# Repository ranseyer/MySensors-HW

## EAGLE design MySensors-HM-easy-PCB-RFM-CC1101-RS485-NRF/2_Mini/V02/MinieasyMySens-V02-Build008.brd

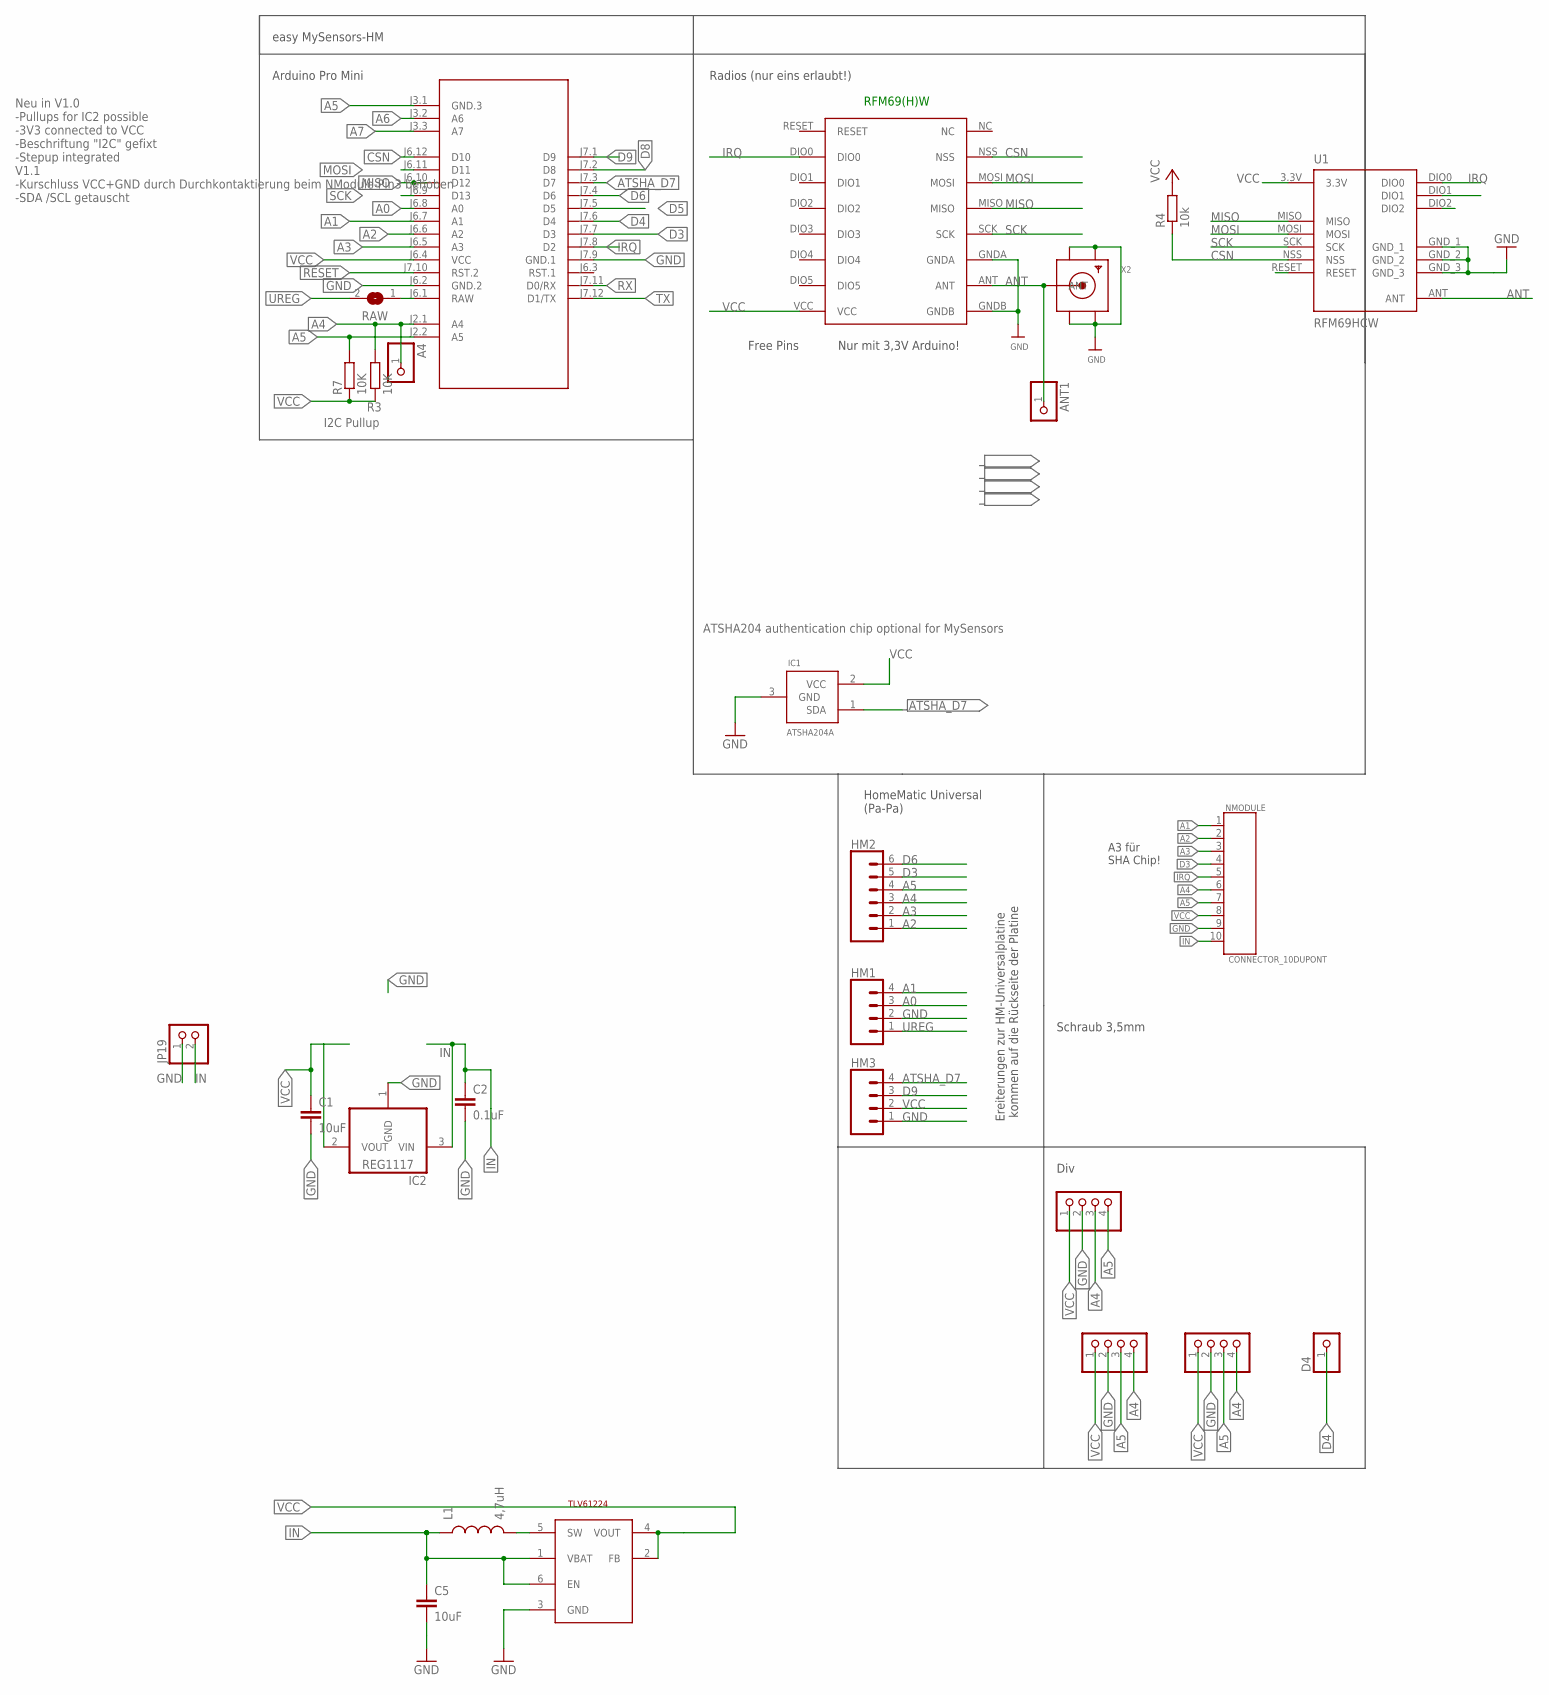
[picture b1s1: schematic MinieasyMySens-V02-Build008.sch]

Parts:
A4: PINHD-1X1; 1X01
ANT1: PINHD-1X1; 1X01
BH1750: PINHD-1X04_2.54-S; 1X04-S
C1: 10uF; C1210
C2: 0.1uF; C1206
C5: 10uF; 0805
D4: PINHD-1X1; 1X01
HM1, HM3: CONN_04; 1X04
HM2: CONN_06SILK_FEMALE_PTH; 1X06
I2C-1, I2C-2: PINHD-1X04_2.54-S; 1X04-S
IC1: ATSHA204A; SOT23
IC2: REG1117; SOT223
JP19: PINHD-1X2; 1X02
L1: 4,7uH; 0805
M1: ARDUINO-PRO-MINI-3.3V#NP; ARDUINO-PRO-MINI#NP
NMODULE: CONNECTOR_10DUPONT; DUPONT_10
R3, R7: 10K; R0805
R4: 10k; M0805
RAW: SJ
RFM69W: RFM69HW; RFM
STEPUP: TLV61224; SOT23-6L
U1: RFM69HCW; RFM69HCW-XXXS2
X2: SMACONNECTOR_EDGE; SMA_EDGELAUNCH

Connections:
A0: HM1.3, M1.J6.8 (A0)
A1: HM1.4, M1.J6.7 (A1), NMODULE.1
A2: HM2.1, M1.J6.6 (A2), NMODULE.2
A3: HM2.2, M1.J6.5 (A3), NMODULE.3
A4: A4.1, BH1750.4, HM2.3, I2C-1.4, I2C-2.3, M1.J2.1 (A4), NMODULE.6, R3.2
A5: BH1750.3, HM2.4, I2C-1.3, I2C-2.4, M1.J2.2 (A5), M1.J3.1 (GND.3), NMODULE.7, R7.2
A6: M1.J3.2 (A6)
A7: M1.J3.3 (A7)
ANT: ANT1.1, RFM69W.ANT, U1.ANT, X2.P (ANT)
ATSHA_D7: HM3.4, IC1.1 (SDA), M1.J7.3 (D7)
CSN: M1.J6.12 (D10), R4.1, RFM69W.NSS, U1.NSS
D3: HM2.5, M1.J7.7 (D3), NMODULE.4
D4: D4.1, M1.J7.6 (D4)
D5: M1.J7.5 (D5)
D6: HM2.6, M1.J7.4 (D6)
D8: M1.J7.2 (D8)
D9: HM3.3, M1.J7.1 (D9)
GND: BH1750.2, C1.2, C2.2, C5.2, HM1.2, HM3.1, I2C-1.2, I2C-2.2, IC1.3 (GND), IC2.1 (GND), JP19.1, M1.J6.2 (GND.2), M1.J7.9 (GND.1), NMODULE.9, RFM69W.GNDA, RFM69W.GNDB, STEPUP.3 (GND), U1.GND_1, U1.GND_2, U1.GND_3, X2.GND@1 (GND4), X2.GND@2 (GND3), X2.GND@3 (GND2), X2.GND@4 (GND1)
IN: C2.1, C5.1, IC2.3 (VIN), JP19.2, L1.1, NMODULE.10, STEPUP.1 (VBAT), STEPUP.6 (EN)
IRQ: M1.J7.8 (D2), NMODULE.5, RFM69W.DIO0, U1.DIO0
MISO: M1.J6.10 (D12), RFM69W.MISO, U1.MISO
MOSI: M1.J6.11 (D11), RFM69W.MOSI, U1.MOSI
unnamed: L1.2, STEPUP.5 (SW)
RAW: M1.J6.1 (RAW), RAW.1
RESET: M1.J7.10 (RST.2)
RX: M1.J7.11 (D0/RX)
SCK: M1.J6.9 (D13), RFM69W.SCK, U1.SCK
TX: M1.J7.12 (D1/TX)
UREG: HM1.1, RAW.2
VCC: BH1750.1, C1.1, HM3.2, I2C-1.1, I2C-2.1, IC1.2 (VCC), IC2.2 (VOUT), M1.J6.4 (VCC), NMODULE.8, R3.1, R4.2, R7.1, RFM69W.VCC, STEPUP.2 (FB), STEPUP.4 (VOUT), U1.3.3V

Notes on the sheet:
easy MySensors-HM
Arduino Pro Mini
Free Pins
ATSHA204 authentication chip optional for MySensors
RFM69(H)W
Nur mit 3,3V Arduino!
A3 für SHA Chip!
Ereiterungen zur HM-Universalplatine kommen auf die Rückseite der Platine
HomeMatic Universal (Pa-Pa)
Schraub 3,5mm
Div
Radios (nur eins erlaubt!)
Neu in V1.0 -Pullups for IC2 possible -3V3 connected to VCC -Beschriftung "I2C" gefixt -Stepup integrated V1.1 -Kurschluss VCC+GND durch Durchkontaktierung beim NModule-Pin3 behoben -SDA /SCL getauscht
I2C Pullup

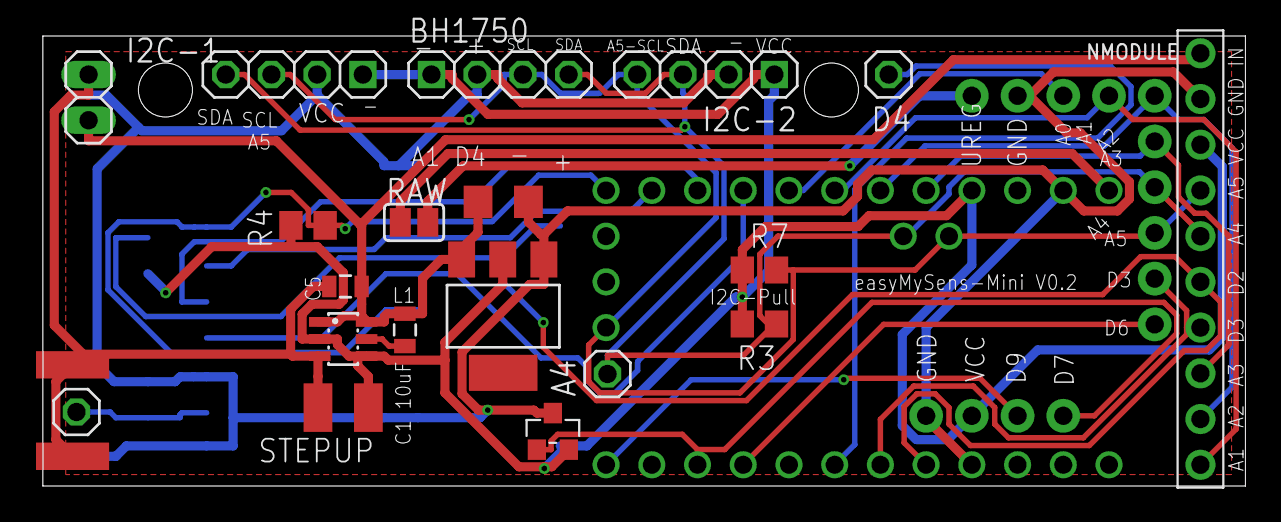
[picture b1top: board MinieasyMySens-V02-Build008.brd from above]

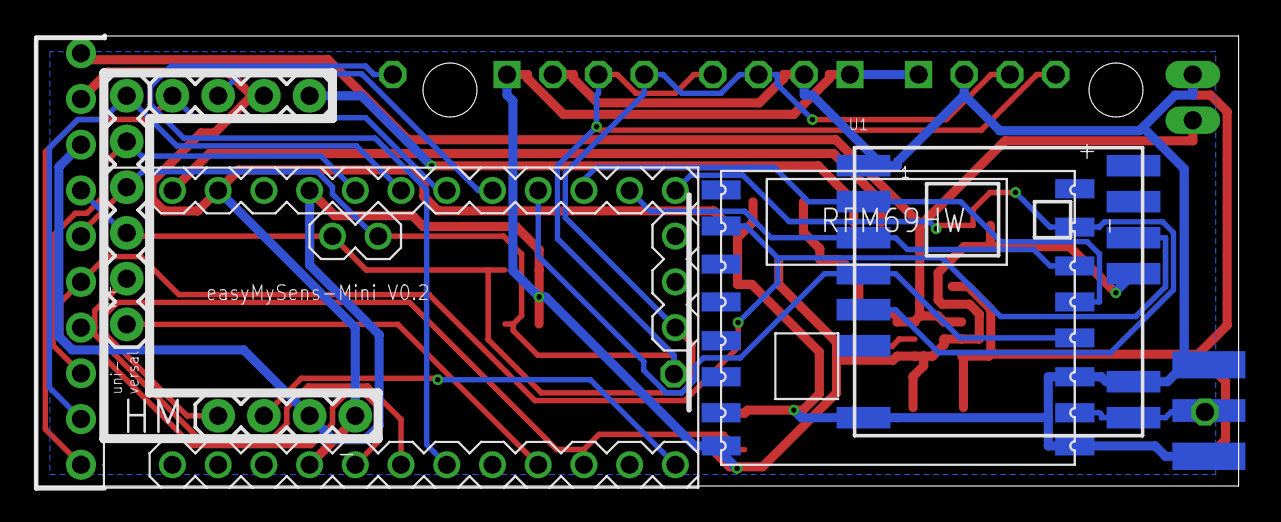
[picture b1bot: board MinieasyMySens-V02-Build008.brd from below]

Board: 2 copper layers, 66.8 x 25.0 mm, 26 parts (7 on the bottom side), 23 nets.

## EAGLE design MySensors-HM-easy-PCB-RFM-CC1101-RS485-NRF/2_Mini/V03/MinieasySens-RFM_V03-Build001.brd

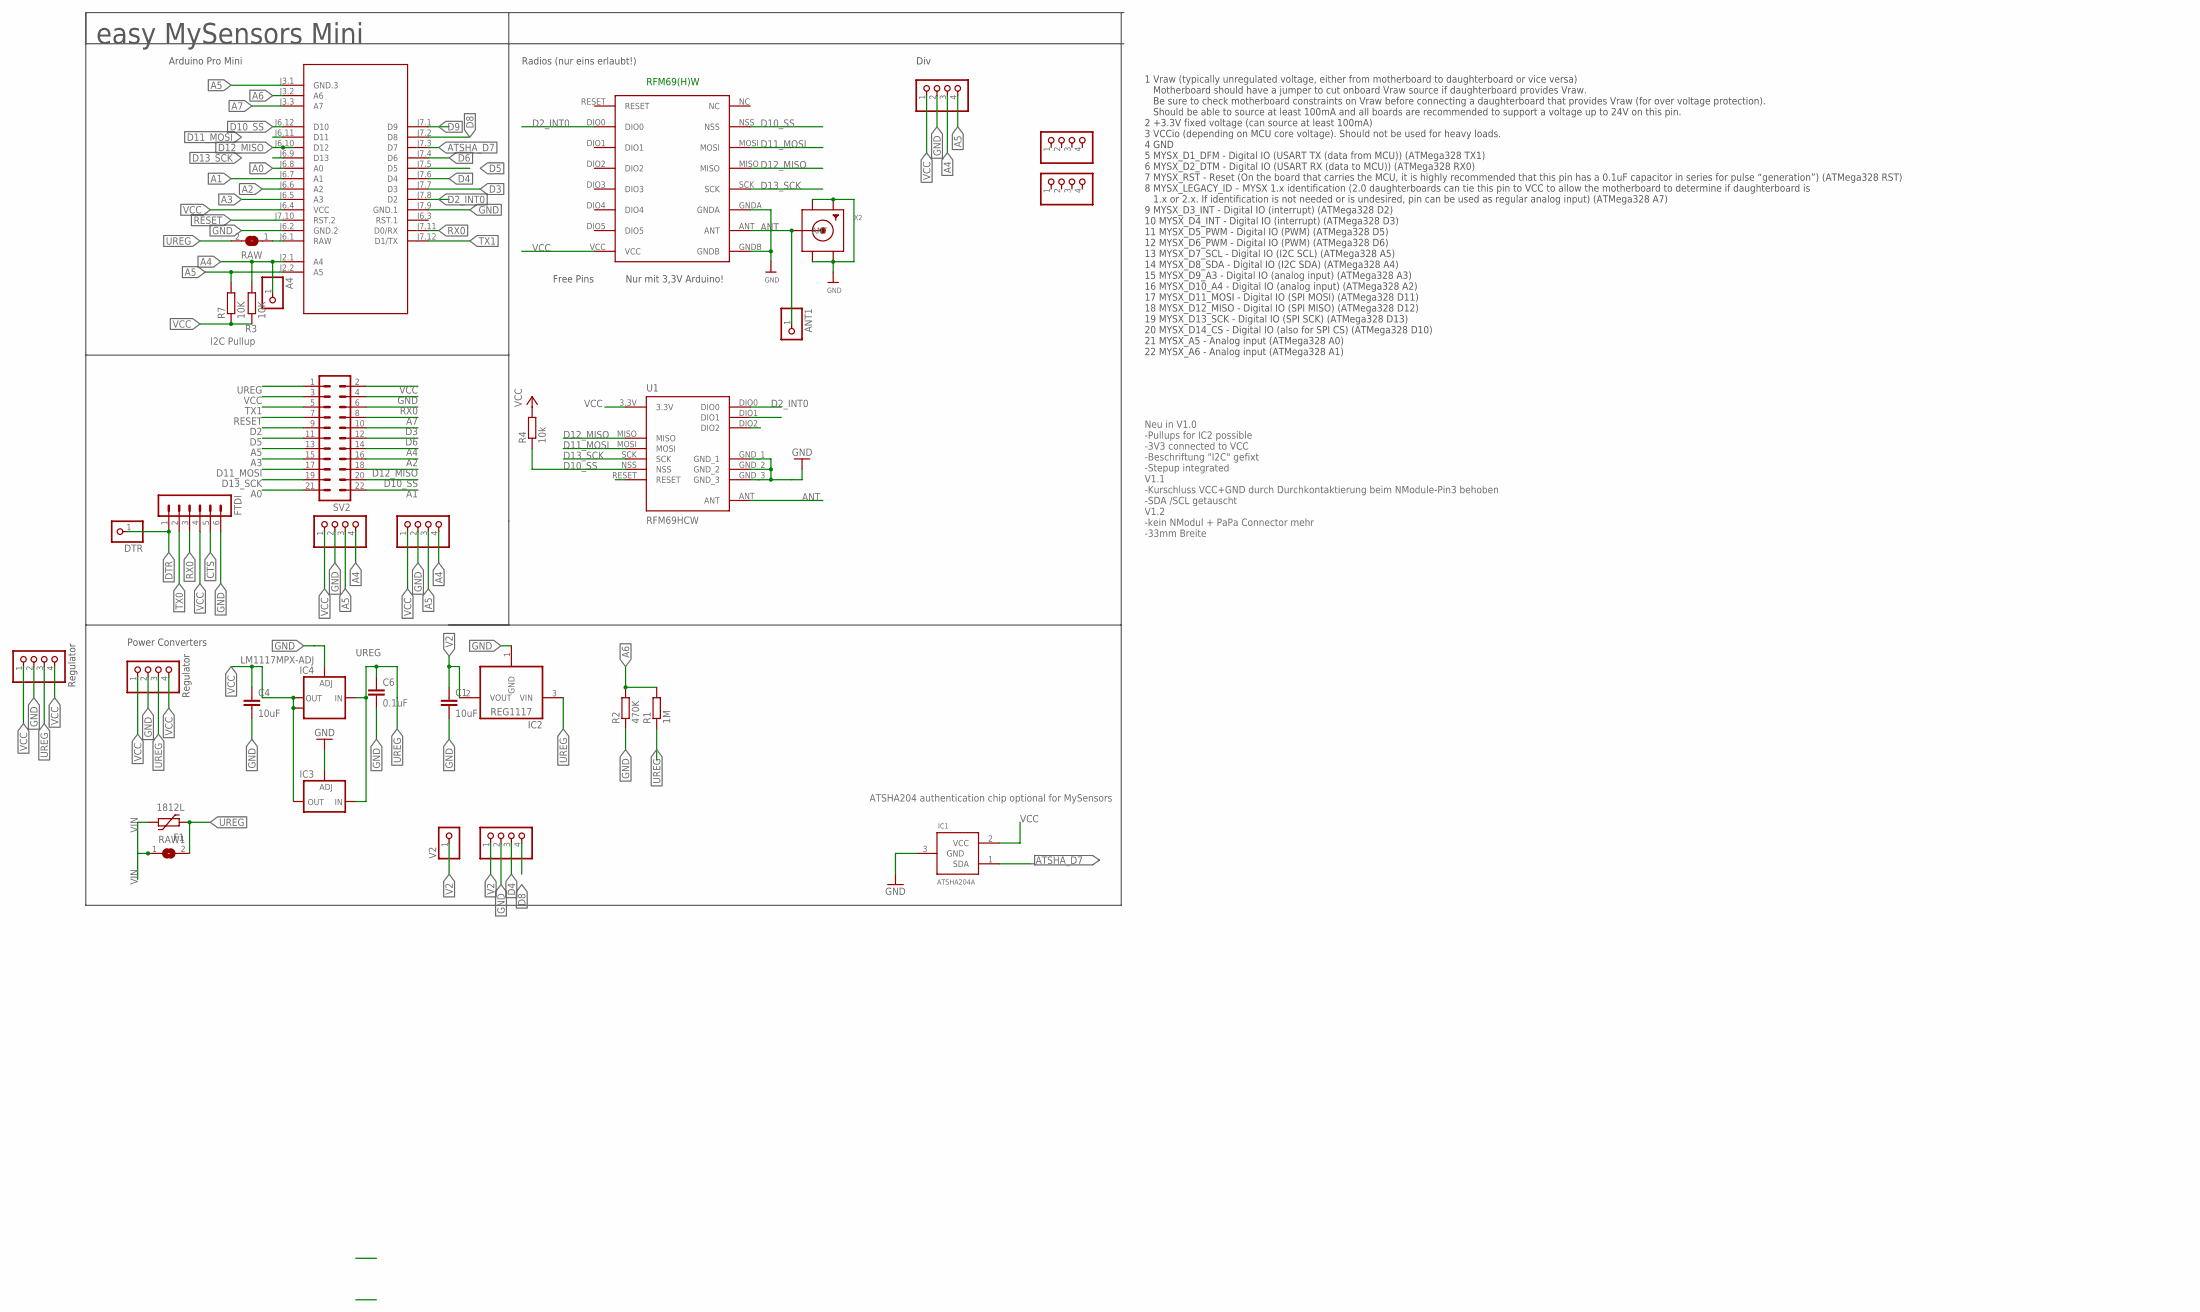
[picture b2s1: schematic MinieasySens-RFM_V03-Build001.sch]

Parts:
A4: PINHD-1X1; 1X01
ANT1: PINHD-1X1; 1X01
BH1750: PINHD-1X04_2.54-S; 1X04-S
C1, C4: 10uF; C1210
C6: 0.1uF; C1206
DTR: PINHD-1X1; 1X01
F1: 1812L
FTDI: MA06-1
I2C-1, I2C-2: PINHD-1X04_2.54-S; 1X04-S
IC1: ATSHA204A; SOT23
IC2: REG1117; SOT223
IC3: LD117ADT50TR; DPACK
IC4: LM1117MPX-ADJ; SOT223
JP1, JP2: PINHD-1X04_2.54-S; 1X04-S
M1: ARDUINO-PRO-MINI-3.3V#NP; ARDUINO-PRO-MINI#NP
R1: 1M; R0805
R2: 470K; R0805
R3, R7: 10K; R0805
R4: 10k; M0805
RAW, RAW1: SJ
RFM69W: RFM69HW; RFM
STEPDWN, STEPDWN1: PINHD-1X04_2.54-S; 1X04-S
SV2: MA11-2
U1: RFM69HCW; RFM69HCW-XXXS2
V2: PINHD-1X1; 1X01
V2-: PINHD-1X04_2.54-S; 1X04-S
X2: SMACONNECTOR_EDGE; SMA_EDGELAUNCH

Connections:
A0: M1.J6.8 (A0), SV2.21
A1: M1.J6.7 (A1), SV2.22
A2: M1.J6.6 (A2), SV2.16
A3: M1.J6.5 (A3), SV2.15
A4: A4.1, BH1750.4, I2C-1.4, I2C-2.3, M1.J2.1 (A4), R3.2, SV2.14
A5: BH1750.3, I2C-1.3, I2C-2.4, M1.J2.2 (A5), M1.J3.1 (GND.3), R7.2, SV2.13
A6: M1.J3.2 (A6), R1.2, R2.2
A7: M1.J3.3 (A7), SV2.8
ANT: ANT1.1, RFM69W.ANT, U1.ANT, X2.P (ANT)
ATSHA_D7: IC1.1 (SDA), M1.J7.3 (D7)
CTS: FTDI.5
D2: SV2.9
D2_INT0: M1.J7.8 (D2), RFM69W.DIO0, U1.DIO0
D3: M1.J7.7 (D3), SV2.10
D4: M1.J7.6 (D4), V2-.3
D5: M1.J7.5 (D5), SV2.11
D6: M1.J7.4 (D6), SV2.12
D8: M1.J7.2 (D8), V2-.4
D9: M1.J7.1 (D9)
D10_SS: M1.J6.12 (D10), R4.1, RFM69W.NSS, SV2.20, U1.NSS
D11_MOSI: M1.J6.11 (D11), RFM69W.MOSI, SV2.17, U1.MOSI
D12_MISO: M1.J6.10 (D12), RFM69W.MISO, SV2.18, U1.MISO
D13_SCK: M1.J6.9 (D13), RFM69W.SCK, SV2.19, U1.SCK
DTR: DTR.1, FTDI.1
GND: BH1750.2, C1.2, C4.2, C6.2, FTDI.6, I2C-1.2, I2C-2.2, IC1.3 (GND), IC2.1 (GND), IC3.1 (ADJ), IC4.1 (ADJ), M1.J6.2 (GND.2), M1.J7.9 (GND.1), R2.1, RFM69W.GNDA, RFM69W.GNDB, STEPDWN.2, STEPDWN1.2, SV2.4, U1.GND_1, U1.GND_2, U1.GND_3, V2-.2, X2.GND@1 (GND4), X2.GND@2 (GND3), X2.GND@3 (GND2), X2.GND@4 (GND1)
RAW: M1.J6.1 (RAW), RAW.1
RESET: M1.J7.10 (RST.2), SV2.7
RX0: FTDI.3, M1.J7.11 (D0/RX), SV2.6
TX0: FTDI.2
TX1: M1.J7.12 (D1/TX), SV2.5
UREG: C6.1, F1.P$1 (1), IC2.3 (VIN), IC3.3 (IN), IC4.3 (IN), R1.1, RAW.2, RAW1.2, STEPDWN.3, STEPDWN1.3, SV2.1
V2: C1.1, IC2.2 (VOUT), V2.1, V2-.1
VCC: BH1750.1, C4.1, FTDI.4, I2C-1.1, I2C-2.1, IC1.2 (VCC), IC3.4 (OUT), IC4.2 (OUT), IC4.TAB (OUT1), M1.J6.4 (VCC), R3.1, R4.2, R7.1, RFM69W.VCC, STEPDWN.1, STEPDWN.4, STEPDWN1.1, STEPDWN1.4, SV2.2, SV2.3, U1.3.3V
VIN: F1.P$2 (2), RAW1.1

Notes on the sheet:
easy MySensors Mini
Arduino Pro Mini
ATSHA204 authentication chip optional for MySensors
Div
Neu in V1.0 -Pullups for IC2 possible -3V3 connected to VCC -Beschriftung "I2C" gefixt -Stepup integrated V1.1 -Kurschluss VCC+GND durch Durchkontaktierung beim NModule-Pin3 behoben -SDA /SCL getauscht V1.2 -kein NModul + PaPa Connector mehr -33mm Breite
I2C Pullup
Power Converters
Regulator
1 Vraw (typically unregulated voltage, either from motherboard to daughterboard or vice versa) Motherboard should have a jumper to cut onboard Vraw source if daughterboard provides Vraw. Be sure to check motherboard constraints on Vraw before connecting a daughterboard that provides Vraw (for over 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
Free Pins
RFM69(H)W
Nur mit 3,3V Arduino!
Radios (nur eins erlaubt!)

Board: 2 copper layers, 33 parts (12 on the bottom side), 30 nets, no tracks yet.

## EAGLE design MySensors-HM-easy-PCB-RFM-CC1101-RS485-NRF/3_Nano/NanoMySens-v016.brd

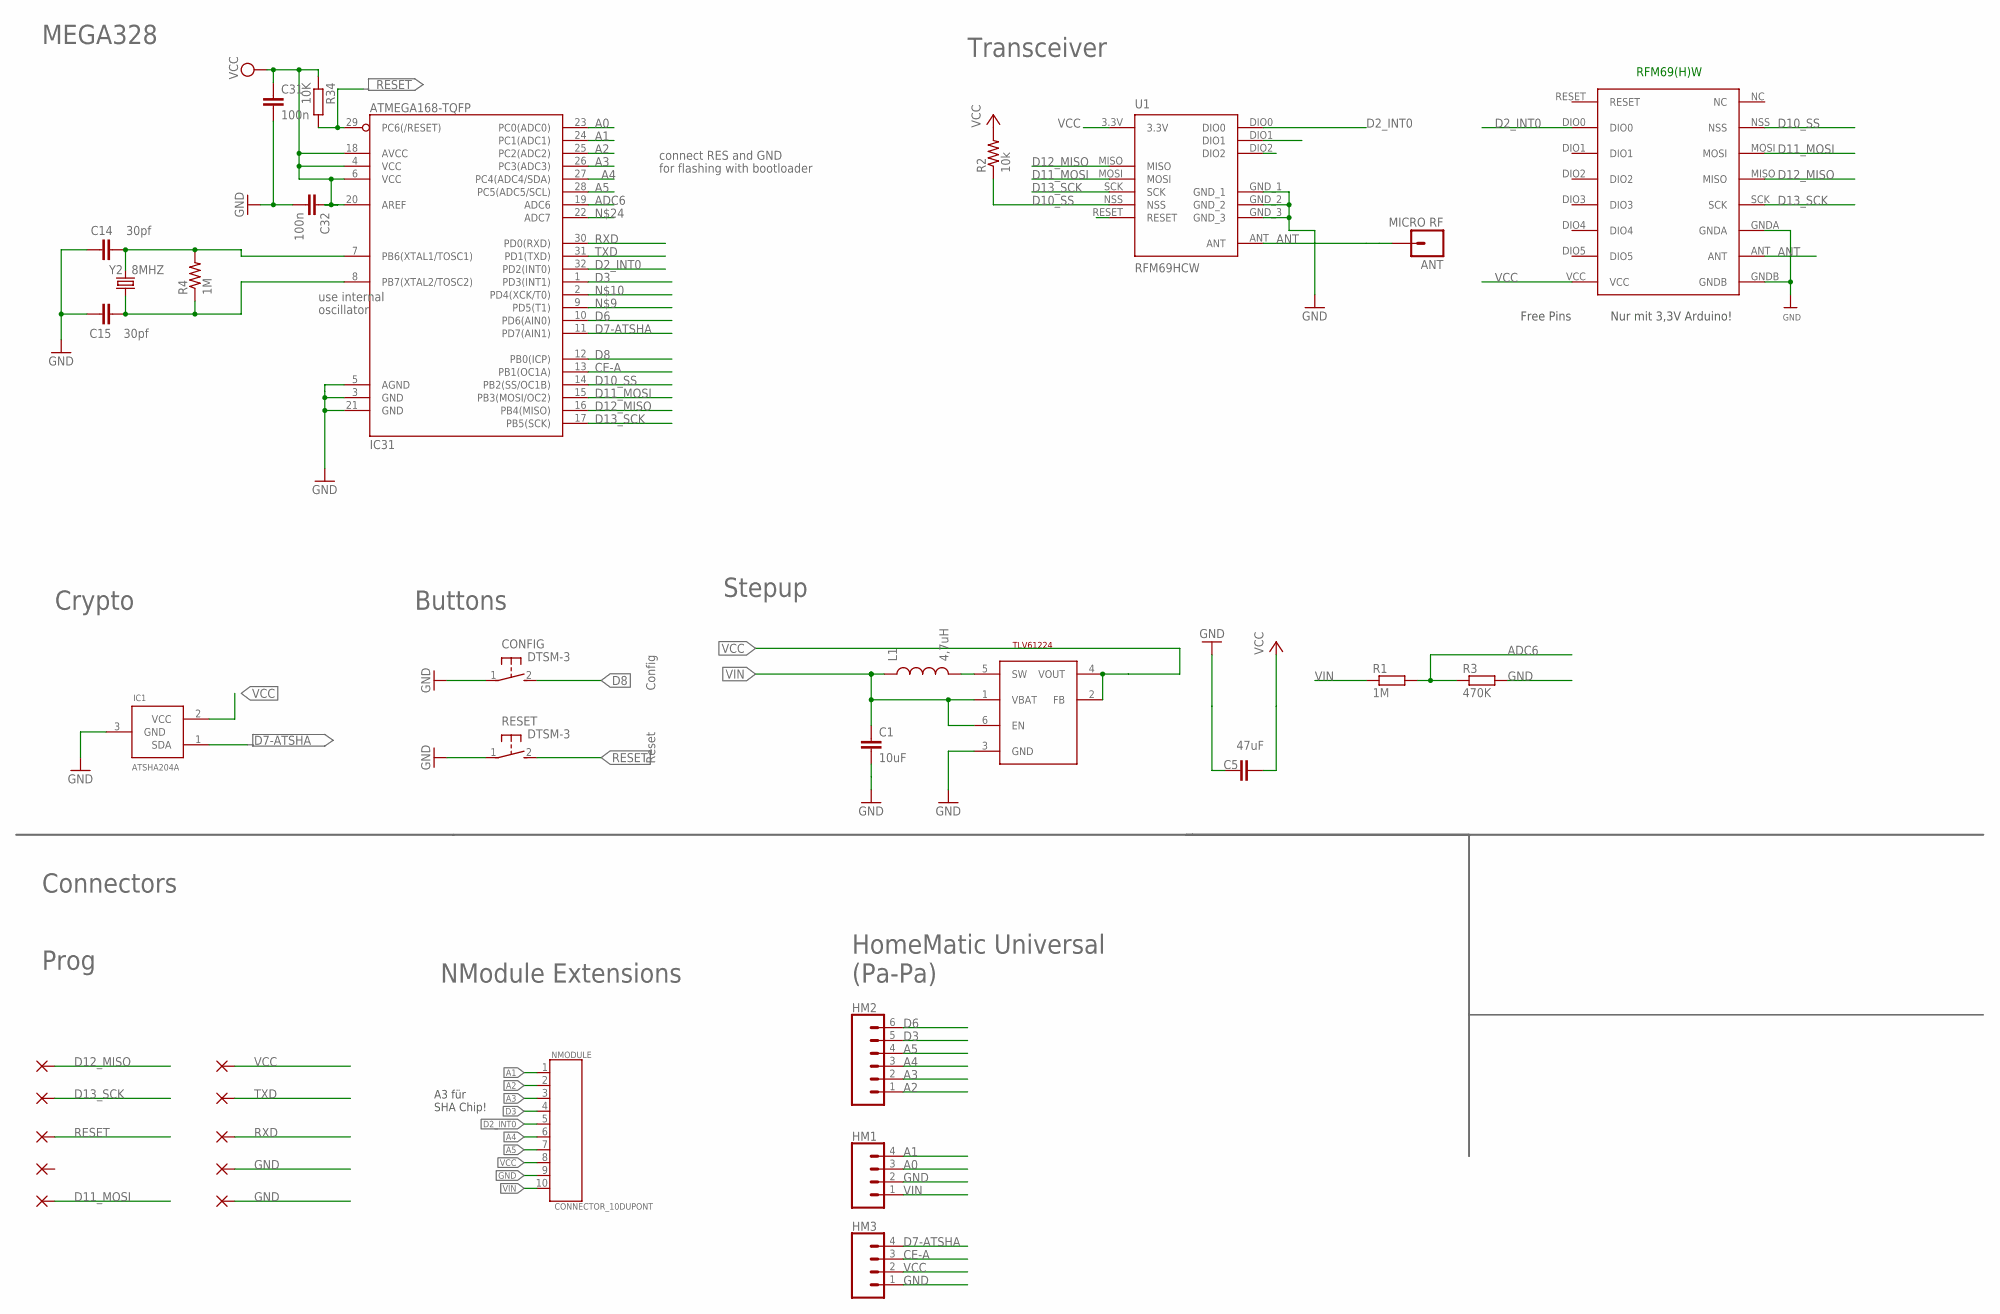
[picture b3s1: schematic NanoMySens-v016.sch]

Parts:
ANT: MICRO RF; 1X01
C1: 10uF; 0805
C5: 47uF; C1210
C14, C15: 30pf; 0805
C31, C32: 100n; C0805
CONFIG: DTSM-3
GND, GND2: WIREPADSMD1,27-254; SMD1,27-2,54
HM1, HM3: CONN_04; 1X04
HM2: CONN_06SILK_FEMALE_PTH; 1X06
IC1: ATSHA204A; SOT23
IC31: ATMEGA168-TQFP; TQFP32-08
L1: 4,7uH; 0805
MISO: WIREPADSMD1,27-254; SMD1,27-2,54
MOSI: WIREPADSMD1,27-254; SMD1,27-2,54
NC: WIREPADSMD1,27-254; SMD1,27-2,54
NMODULE: CONNECTOR_10DUPONT; DUPONT_10
R1: 1M; R0805
R2: 10k; 0805
R3: 470K; R0805
R4: 1M; 0805
R34: 10K; R0805
RESET: DTSM-3
RFM69W: RFM69HW; RFM
RST: WIREPADSMD1,27-254; SMD1,27-2,54
RXD: WIREPADSMD1,27-254; SMD1,27-2,54
SCK: WIREPADSMD1,27-254; SMD1,27-2,54
STEPUP: TLV61224; SOT23-6L
TXD: WIREPADSMD1,27-254; SMD1,27-2,54
U1: RFM69HCW; RFM69HCW-XXXS2
VCC: WIREPADSMD1,27-254; SMD1,27-2,54
Y2: 8MHZ; CRYSTAL-TXC-7A

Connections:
A0: HM1.3, IC31.23 (PC0(ADC0))
A1: HM1.4, IC31.24 (PC1(ADC1)), NMODULE.1
A2: HM2.1, IC31.25 (PC2(ADC2)), NMODULE.2
A3: HM2.2, IC31.26 (PC3(ADC3)), NMODULE.3
A4: HM2.3, IC31.27 (PC4(ADC4/SDA)), NMODULE.6
A5: HM2.4, IC31.28 (PC5(ADC5/SCL)), NMODULE.7
ADC6: IC31.19 (ADC6), R1.2, R3.1
ANT: ANT.1, RFM69W.ANT, U1.ANT
CE-A: HM3.3, IC31.13 (PB1(OC1A))
D2_INT0: IC31.32 (PD2(INT0)), NMODULE.5, RFM69W.DIO0, U1.DIO0
D3: HM2.5, IC31.1 (PD3(INT1)), NMODULE.4
D6: HM2.6, IC31.10 (PD6(AIN0))
D7-ATSHA: HM3.4, IC1.1 (SDA), IC31.11 (PD7(AIN1))
D8: CONFIG.2, IC31.12 (PB0(ICP))
D10_SS: IC31.14 (PB2(SS/OC1B)), R2.1, RFM69W.NSS, U1.NSS
D11_MOSI: IC31.15 (PB3(MOSI/OC2)), MOSI.1, RFM69W.MOSI, U1.MOSI
D12_MISO: IC31.16 (PB4(MISO)), MISO.1, RFM69W.MISO, U1.MISO
D13_SCK: IC31.17 (PB5(SCK)), RFM69W.SCK, SCK.1, U1.SCK
GND: C1.2, C5.1, C14.1, C15.1, C31.2, C32.2, CONFIG.1, GND.1, GND2.1, HM1.2, HM3.1, IC1.3 (GND), IC31.3 (GND), IC31.5 (AGND), IC31.21 (GND), NMODULE.9, R3.2, RESET.1, RFM69W.GNDA, RFM69W.GNDB, STEPUP.3 (GND), U1.GND_1, U1.GND_2, U1.GND_3
unnamed: C14.2, IC31.7 (PB6(XTAL1/TOSC1)), R4.2, Y2.P$2 (2)
unnamed: L1.2, STEPUP.5 (SW)
unnamed: C15.2, IC31.8 (PB7(XTAL2/TOSC2)), R4.1, Y2.P$1 (1)
RESET: IC31.29 (PC6(/RESET)), R34.2, RESET.2, RST.1
RXD: IC31.30 (PD0(RXD)), RXD.1
TXD: IC31.31 (PD1(TXD)), TXD.1
VCC: C5.2, C31.1, C32.1, HM3.2, IC1.2 (VCC), IC31.4 (VCC), IC31.6 (VCC), IC31.18 (AVCC), IC31.20 (AREF), NMODULE.8, R2.2, R34.1, RFM69W.VCC, STEPUP.2 (FB), STEPUP.4 (VOUT), U1.3.3V, VCC.1
VIN: C1.1, HM1.1, L1.1, NMODULE.10, R1.1, STEPUP.1 (VBAT), STEPUP.6 (EN)

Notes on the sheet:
MEGA328
use internal
oscillator
connect RES and GND
for flashing with bootloader
A3 für SHA Chip!
Config
Reset
Crypto
Buttons
Stepup
Transceiver
Connectors
Prog
NModule Extensions
HomeMatic Universal (Pa-Pa)
Free Pins
RFM69(H)W
Nur mit 3,3V Arduino!

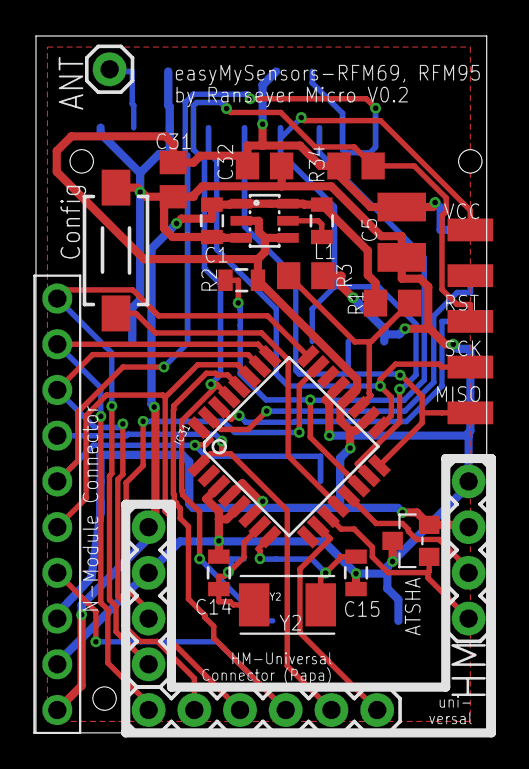
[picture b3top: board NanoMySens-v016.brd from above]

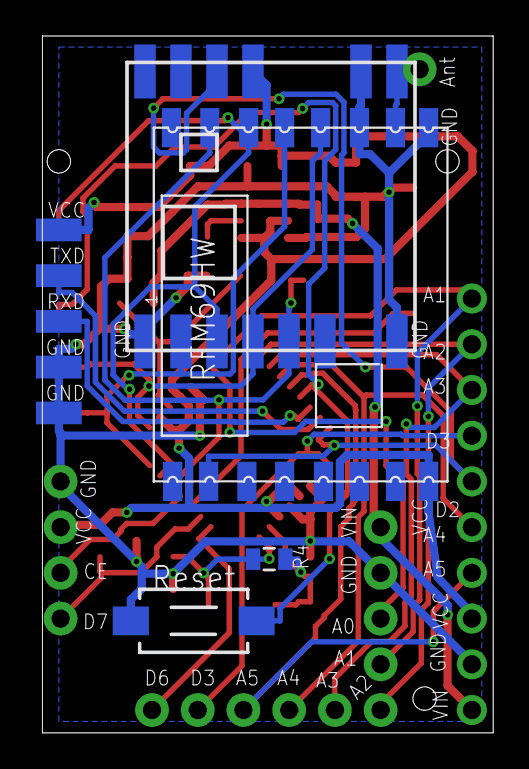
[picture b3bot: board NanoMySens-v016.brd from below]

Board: 2 copper layers, 25.0 x 38.7 mm, 35 parts (9 on the bottom side), 27 nets.

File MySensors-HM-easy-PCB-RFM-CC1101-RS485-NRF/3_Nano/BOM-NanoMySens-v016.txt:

Stückliste exportiert aus D:/GitHub/MySensors-HW/MySensors-HM-easy-PCB-RFM-CC1101-RS485-NRF/3_Nano/NanoMySens-v016.sch am 22.12.2017 12:21

Part    Value              Device                 Package        Description                                                                                                     PROD_ID   
ANT     MICRO RF           M01PTH                 1X01           Header 1                                                                                                                  
C1      10uF               CAP0805                0805           Capacitor                                                                                                                 
C5      47uF               C-EUC1210              C1210          CAPACITOR, European symbol                                                                                                
C14     30pf               CAP0805                0805           Capacitor                                                                                                                 
C15     30pf               CAP0805                0805           Capacitor                                                                                                                 
C31     100n               C-EUC0805              C0805          CAPACITOR, European symbol                                                                                                
C32     100n               C-EUC0805              C0805          CAPACITOR, European symbol                                                                                                
CONFIG  DTSM-3             DTSM-3                 DTSM-3         Diptronics SMD button 6x3.5 mm                                                                                            
GND     WIREPADSMD1,27-254 WIREPADSMD1,27-254     SMD1,27-2,54   Wire PAD connect wire on PCB                                                                                              
GND2    WIREPADSMD1,27-254 WIREPADSMD1,27-254     SMD1,27-2,54   Wire PAD connect wire on PCB                                                                                              
HM1                        CONN_04                1X04           Multi connection point. Often used as Generic Header-pin footprint for 0.1 inch spaced/style header connections CONN-09696
HM2                        CONN_06SILK_FEMALE_PTH 1X06           Multi connection point. Often used as Generic Header-pin footprint for 0.1 inch spaced/style header connections CONN-08437
HM3                        CONN_04                1X04           Multi connection point. Often used as Generic Header-pin footprint for 0.1 inch spaced/style header connections CONN-09696
IC1     ATSHA204A          ATSHA204A              SOT23                                                                                                                                    
IC31    ATMEGA168-TQFP     ATMEGA168-TQFP         TQFP32-08      Atmel Atmega 168/328/328P                                                                                                 
L1      4,7uH              INDUCTOR0805           0805           Inductors                                                                                                                 
MISO    WIREPADSMD1,27-254 WIREPADSMD1,27-254     SMD1,27-2,54   Wire PAD connect wire on PCB                                                                                              
MOSI    WIREPADSMD1,27-254 WIREPADSMD1,27-254     SMD1,27-2,54   Wire PAD connect wire on PCB                                                                                              
NC      WIREPADSMD1,27-254 WIREPADSMD1,27-254     SMD1,27-2,54   Wire PAD connect wire on PCB                                                                                              
NMODULE CONNECTOR_10DUPONT CONNECTOR_10DUPONT     DUPONT_10                                                                                                                                
R1      1M                 R-EU_R0805             R0805          RESISTOR, European symbol                                                                                                 
R2      10k                RESISTOR0805-RES       0805           Resistor                                                                                                                  
R3      470K               R-EU_R0805             R0805          RESISTOR, European symbol                                                                                                 
R4      1M                 RESISTOR0805-RES       0805           Resistor                                                                                                                  
R34     10K                R-EU_R0805             R0805          RESISTOR, European symbol                                                                                                 
RESET   DTSM-3             DTSM-3                 DTSM-3         Diptronics SMD button 6x3.5 mm                                                                                            
RFM69W  RFM69HW            RFM69HW                RFM                                                                                                                                      
RST     WIREPADSMD1,27-254 WIREPADSMD1,27-254     SMD1,27-2,54   Wire PAD connect wire on PCB                                                                                              
RXD     WIREPADSMD1,27-254 WIREPADSMD1,27-254     SMD1,27-2,54   Wire PAD connect wire on PCB                                                                                              
SCK     WIREPADSMD1,27-254 WIREPADSMD1,27-254     SMD1,27-2,54   Wire PAD connect wire on PCB                                                                                              
STEPUP  TLV61224           TI-TLV61224            SOT23-6L                                                                                                                                 
TXD     WIREPADSMD1,27-254 WIREPADSMD1,27-254     SMD1,27-2,54   Wire PAD connect wire on PCB                                                                                              
U1      RFM69HCW           RFM69HCW               RFM69HCW-XXXS2                                                                                                                           
VCC     WIREPADSMD1,27-254 WIREPADSMD1,27-254     SMD1,27-2,54   Wire PAD connect wire on PCB                                                                                              
Y2      8MHZ               CRYSTALTXC-7A          CRYSTAL-TXC-7A Various standard crystals. Proven footprints.

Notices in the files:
parts and their libraries:
diy-modules: Released under the Creative Commons Attribution 4.0 International License: http://creativecommons.org/licenses/by/4.0
SparkFun-Connectors: Licensing: Creative Commons ShareAlike 4.0 International - https://creativecommons.org/licenses/by-sa/4.0
